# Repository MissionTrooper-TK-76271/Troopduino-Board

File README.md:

# Troopduino-Board
Troopduino Voice Changer and Effects Board

https://github.com/BipeFlyer/Troopduino

This project uses an Arduino nano to create clicks and static when talking.  
Features:
<ul>
  <li>Voice changer
  <ul>
  <li>Bandpass Filter</li>
  <li>Bitcrusher</li>
  <li>Reverb</li>
</ul>
  </li>
  <li>PTT (Push to Talk) Mode</li>
  <li>Voice Activation Mode</li>
  <li>Sound Effects</li>
  <li>Looping Background Effects</li>
</ul>

To Complete this project you will need:
<ul>
  <li>Arduino Nano</li>
  <li>DFPlayer Mini</li>
  <li>OSH Troopduino V1.1
  <li>Adafruit Electret Microphone Amplifier - MAX4466 with Adjustable Gain https://www.adafruit.com/product/1063</li>
  <li>3.5mm Phone Jack	https://www.mouser.ca/ProductDetail/490-MJ-3523-SMT-TR</li>
  <li>C1, C2 Capacitor	https://www.mouser.ca/ProductDetail/603-CC805ZRY5V9BB104</li>
  <li>R1	2.2K Ohm	https://www.mouser.ca/ProductDetail/652-CR0805JW-222ELF</li>
  <li>R2, R4, R5	1K Ohm	https://www.mouser.ca/ProductDetail/652-CR0805JW-102ELF</li>
  <li>R3	1.5K Ohm	https://www.mouser.ca/ProductDetail/652-CR0805JW-152ELF</li>
</ul>

See the BOM for components available at Digikey, Mouser etc.

<a href="https://oshpark.com/shared_projects/eVuWWTMU"></img></a>

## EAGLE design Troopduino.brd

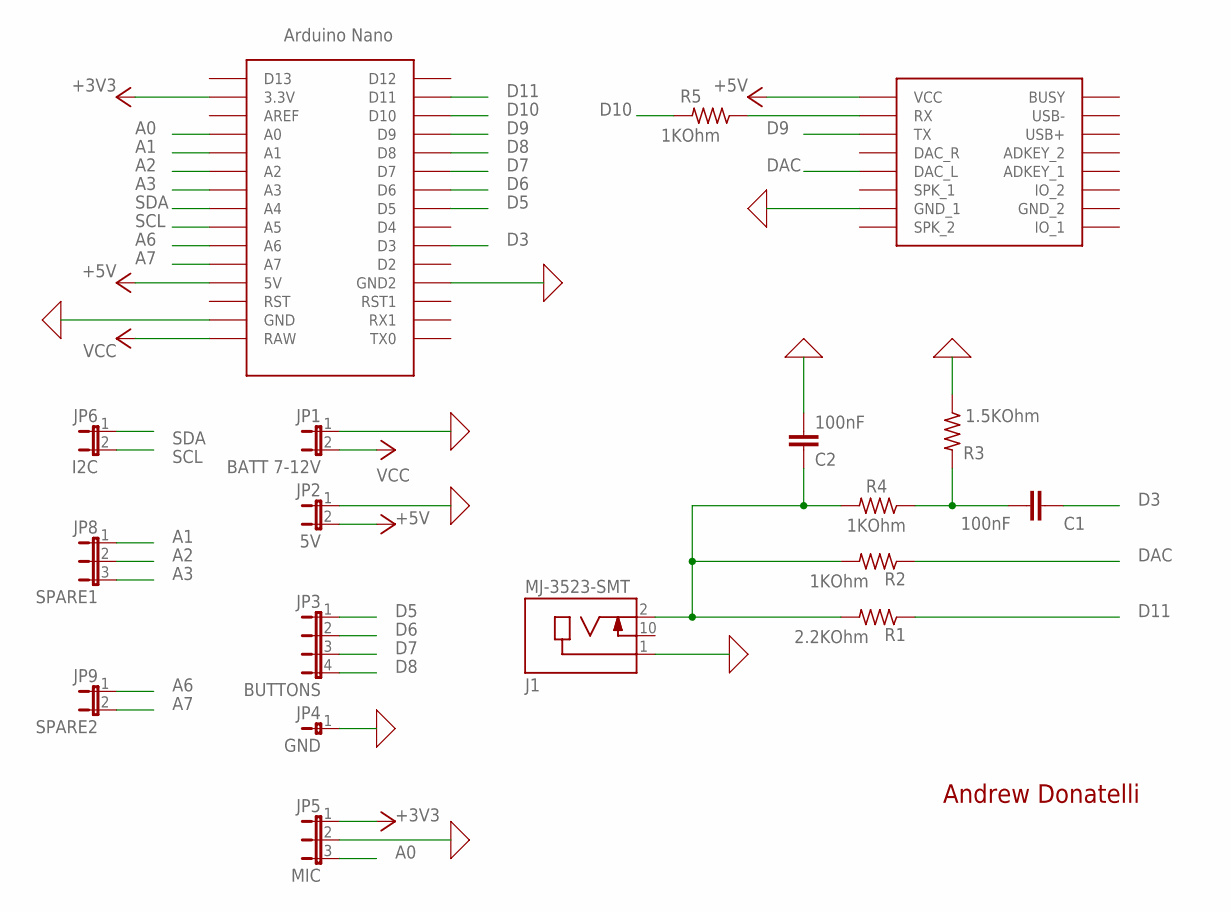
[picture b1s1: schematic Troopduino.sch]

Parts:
C1, C2: 100nF; C0805
J1: MJ-3523-SMT; CUI_MJ-3523-SMT
JP1: BATT 7-12V; JP1
JP2: 5V; JP1
JP3: BUTTONS; JP4
JP4: GND; JP0
JP5: MIC; JP2
JP6: I2C; JP1
JP8: SPARE1; JP2
JP9: SPARE2; JP1
R1: 2.2KOhm; M0805
R2, R4, R5: 1KOhm; M0805
R3: 1.5KOhm; M0805
U$1: DFPLAYER
U$2: NANO

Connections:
0: C2.1, J1.1, JP1.1, JP2.1, JP4.1, JP5.2, R3.1, U$1.GND_1, U$2.GND, U$2.GND1 (GND2)
+3V3: JP5.1, U$2.3.3V
+5V: JP2.2, U$1.VCC, U$2.5V
A0: JP5.3, U$2.A0
A1: JP8.1, U$2.A1
A2: JP8.2, U$2.A2
A3: JP8.3, U$2.A3
A6: JP9.1, U$2.A6
A7: JP9.2, U$2.A7
D3: C1.1, U$2.D3
D5: JP3.1, U$2.D5
D6: JP3.2, U$2.D6
D7: JP3.3, U$2.D7
D8: JP3.4, U$2.D8
D9: U$1.TX, U$2.D9
D10: R5.2, U$2.D10
D11: R1.1, U$2.D11
DAC: R2.1, U$1.DAC_L
unnamed: R5.1, U$1.RX
unnamed: C1.2, R3.2, R4.1
unnamed: C2.2, J1.2, R1.2, R2.2, R4.2
SCL: JP6.2, U$2.A5
SDA: JP6.1, U$2.A4
VCC: JP1.2, U$2.RAW

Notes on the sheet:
Andrew Donatelli

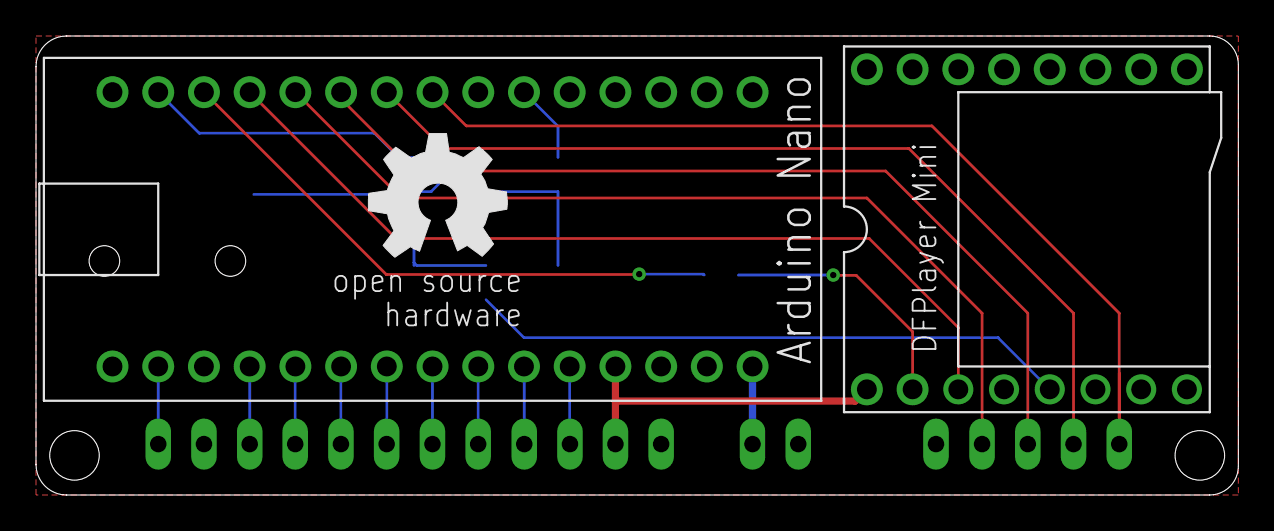
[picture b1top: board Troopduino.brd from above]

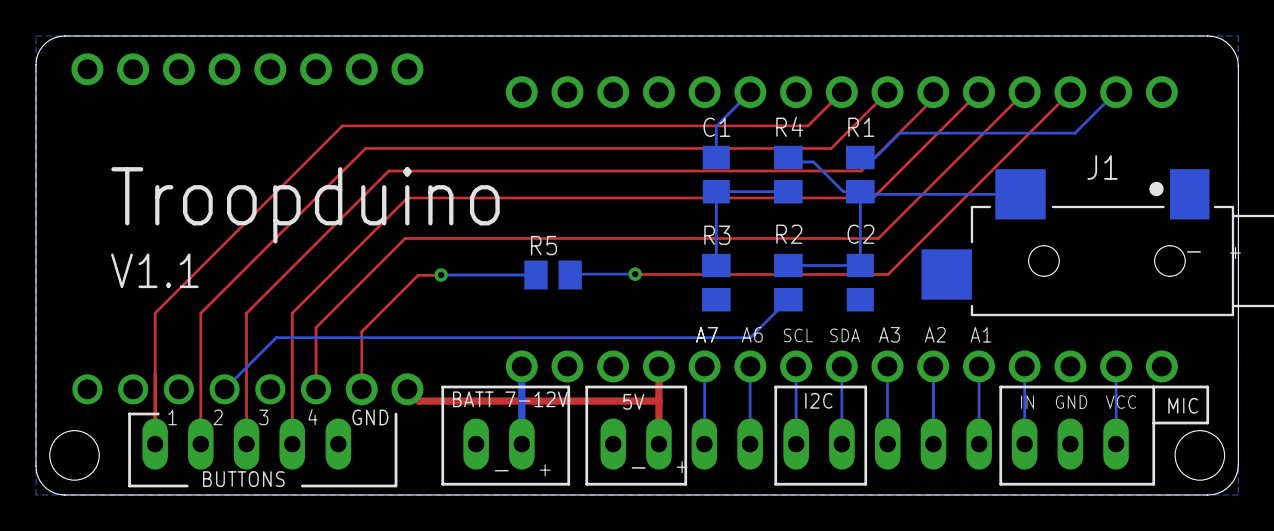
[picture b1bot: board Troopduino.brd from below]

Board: 2 copper layers, 66.8 x 25.5 mm, 19 parts (16 on the bottom side), 24 nets.

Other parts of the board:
U$3: OSHW_8MM

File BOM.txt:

Part		Value		Package	Notes
C1		100nF		C0805	
C2		100nF		C0805	
J1		MJ-3523-SMT		
R1		2.2KOhm		M0805	
R2		1KOhm		M0805	
R3		1.5KOhm		M0805	
R4		1KOhm		M0805	
R5		1KOhm		M0805	Optional - Required if using regulated 5V power or 7 to 12v battery.  Not required for 1 Cell lithium-Ion battery. (Solder bridge or use 0Ohm)

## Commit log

2019-05-20 Update LICENSE
2020-06-01 Added finished Troopduino example
2020-06-01 Product recommendation and troubleshooting
2020-06-01 Listed BOM to front
    Friends and I completely missed the BOM pieces for the capacitors and resistors when we built our own. It will be easier to see and recognize as part of the listed parts needed.
